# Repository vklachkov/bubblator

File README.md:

# Bubblator

> [!WARNING]
> This project is unfinished. Nothing is known to work yet. Do not use this board with real bubble-memory modules. It may damage rare hardware. Please wait for tested hardware, firmware, and clear operating instructions.

Bubblator is an experimental board for reading, writing, and attempting to restore Intel 7110 bubble-memory modules.

It follows the Intel Bubble Memory System design and uses the following main parts:

- Intel 7110 / 7110A(Z) One Megabit Bubble Memory Unit
- Intel 7220-1 Bubble Memory Controller
- Intel 7230 Current Pulse Generator
- Intel 7242 Formatter/Sense Amplifier
- Intel 7250 Coil Predriver
- 2x Intel 7254 driver transistors
- Arduino Nano

Firmware serial commands are described in [firmware/COMMANDS.md](firmware/COMMANDS.md).

## Documentation Used

The following Intel documents were used during development:

- [Megabits to Megabytes: Bubble Memory System Design and Board Layout (AP-187, 1984)](https://archive.org/details/bitsavers_intelbubbl87MegabitsToMegabytesBubbleMemorySystemD_3867950) - system design, board layout, and implementation guidance.
- [Intel Bubble Memory Design Handbook](https://archive.org/details/IntelBubbleMemoryDesignHandbook) - bubble-memory principles and design reference.
- [Intel BPK72 Bubble Storage Prototype Kit](https://web.archive.org/web/20190419090939/https://www.wolfgangrobel.de/museum/files_bubble5/intel%20BPK72%20Prototype%20kit%20users%20manual.pdf) - reference prototype system and kit documentation.
- [Intel 7220 Controller for 1Mbit BPK 70A Bubble Memory Subsystem](https://web.archive.org/web/20250912182130/https://wolfgangrobel.de/museum/files_bubble5/intel%207220%20bubble%20memory%20controller.pdf) - datasheet for the Intel 7220 bubble-memory controller.

Further project background:
- [ArduBubble / ReBubbling on the Unix Haters Wiki](https://wiki.unix-haters.org/doku.php?id=grid:rebubbling)

## Authors

- **sabur** - original firmware code.
- **grm** - initial hardware design.
- **BOOtak** - created the second PCB revision and assembled the prototype.
- **vklachkov** - continued the work of others.

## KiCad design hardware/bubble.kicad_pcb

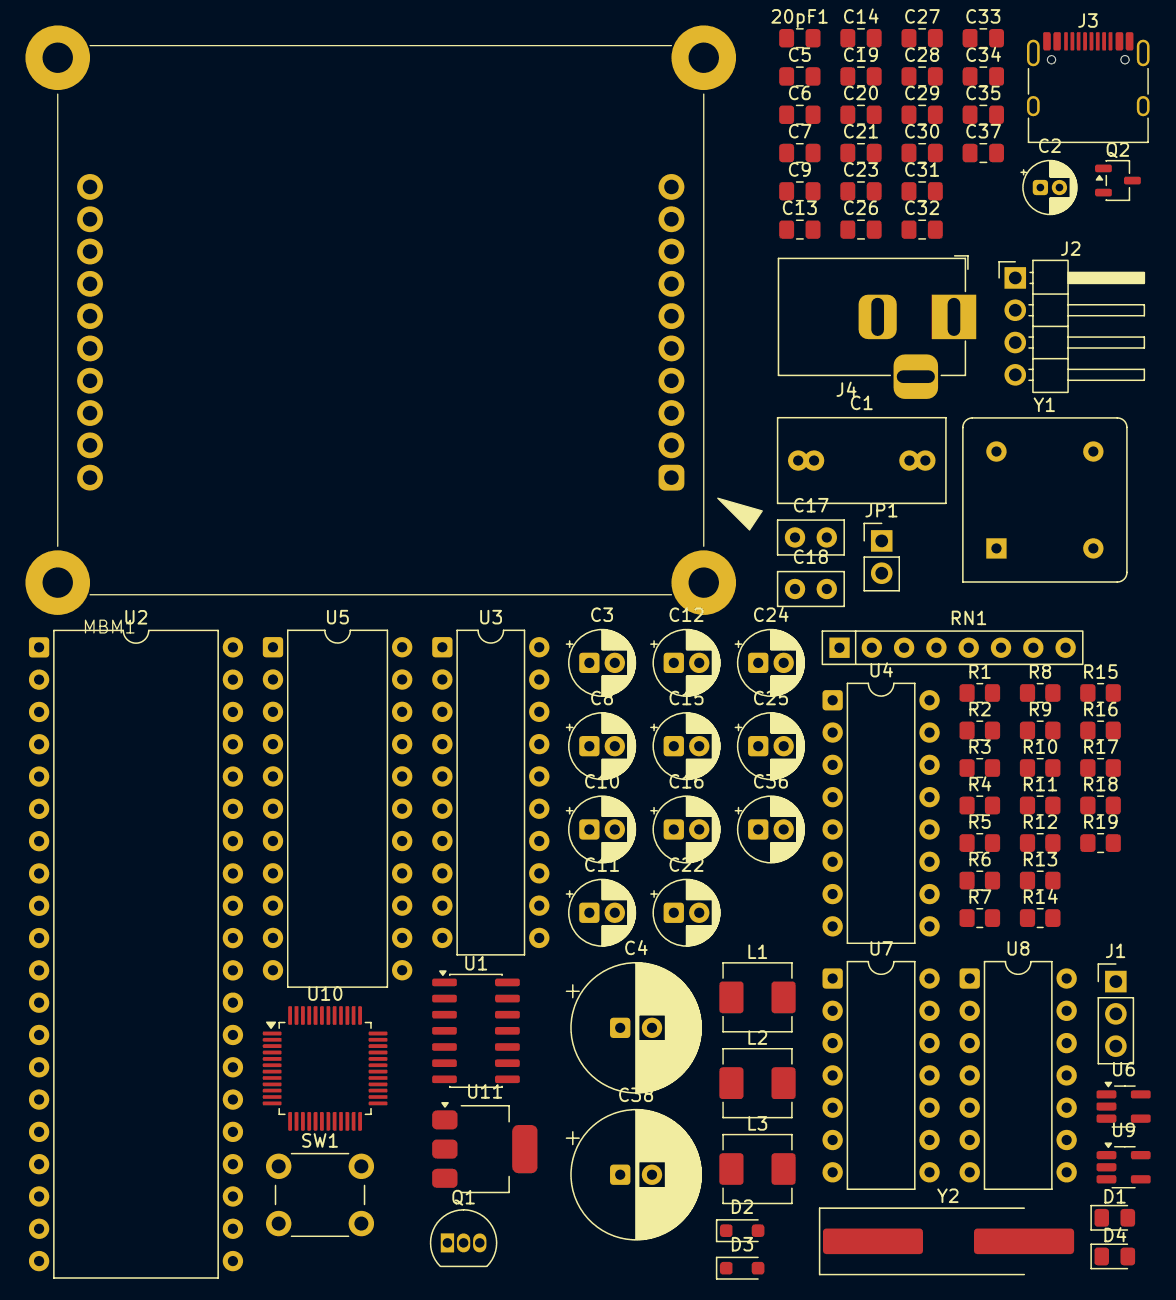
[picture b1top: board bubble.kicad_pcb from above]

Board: 4 copper layers, 88 parts (0 on the bottom side), 103 nets, no tracks yet.

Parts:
20pF1: C; C_0805_2012Metric_Pad1.18x1.45mm_HandSolder
C1: 0.33 uF; C_Rect_L13.0mm_W6.5mm_P7.50mm_P10.00mm
C2: 22uF; CP_Radial_D4.0mm_P1.50mm
C3, C8, C10, C11, C36: 47uF; CP_Radial_D5.0mm_P2.00mm
C4, C38: 150uF; CP_Radial_D10.0mm_P2.50mm
C5, C6, C7, C9, C13, C14, C19, C20, C21, C31, C32, C33, C35, C37: 0.1uF; C_0805_2012Metric_Pad1.18x1.45mm_HandSolder
C12, C15, C22, C24, C25: 22uF; CP_Radial_D5.0mm_P2.00mm
C16: 22uF 25V; CP_Radial_D5.0mm_P2.00mm
C17, C18: 120 pF 100V 5%; C_Disc_D5.0mm_W2.5mm_P2.50mm
C23: 2.2 uF; C_0805_2012Metric_Pad1.18x1.45mm_HandSolder
C26, C27: 0.01 uF; C_0805_2012Metric_Pad1.18x1.45mm_HandSolder
C28: 10 uF; C_0805_2012Metric_Pad1.18x1.45mm_HandSolder
C29: 20pF; C_0805_2012Metric_Pad1.18x1.45mm_HandSolder
C30, C34: 22uF; C_0805_2012Metric_Pad1.18x1.45mm_HandSolder
D1: POWER FAILED LED; LED_0805_2012Metric_Pad1.15x1.40mm_HandSolder
D2, D3: D; D_SOD-323_HandSoldering
D4: LED; LED_0805_2012Metric_Pad1.15x1.40mm_HandSolder
J1: Conn_01x03_Pin; PinHeader_1x03_P2.54mm_Vertical
J2: Conn_01x04_Pin; PinHeader_1x04_P2.54mm_Horizontal
J3: USB-C; USB_C_Receptacle_HRO_TYPE-C-31-M-12
J4: 12V Power; BarrelJack_Horizontal
JP1: Only for reseed; PinHeader_1x02_P2.54mm_Vertical
L1, L2, L3: 0.22 uH; L_APV_APH0530
MBM1: i7110; MBM_socket
Q1: BS170; TO-92_Inline
Q2: DTC113Z; SOT-23-3
R1, R2, R13, R15, R16: 5.1k; R_0805_2012Metric_Pad1.20x1.40mm_HandSolder
R3: 3.48k; R_0805_2012Metric_Pad1.20x1.40mm_HandSolder
R4: 10; R_0805_2012Metric_Pad1.20x1.40mm_HandSolder
R5: 300; R_0805_2012Metric_Pad1.20x1.40mm_HandSolder
R6: 47; R_0805_2012Metric_Pad1.20x1.40mm_HandSolder
R7: 1k; R_0805_2012Metric_Pad1.20x1.40mm_HandSolder
R8: 3.9k; R_0805_2012Metric_Pad1.20x1.40mm_HandSolder
R9: 5.5k; R_0805_2012Metric_Pad1.20x1.40mm_HandSolder
R10: 33k; R_0805_2012Metric_Pad1.20x1.40mm_HandSolder
R11, R12: 5.1; R_0805_2012Metric_Pad1.20x1.40mm_HandSolder
R14: 300Ohm; R_0805_2012Metric_Pad1.20x1.40mm_HandSolder
R17, R18: 22; R_0805_2012Metric_Pad1.20x1.40mm_HandSolder
R19: 1.5k; R_0805_2012Metric_Pad1.20x1.40mm_HandSolder
RN1: 1k; R_Array_SIP8
SW1: Reset; SW_PUSH_6mm_H5mm
U1: 74LS74; SOIC-14_3.9x8.7mm_P1.27mm
U2: i7220; DIP-40_W15.24mm
U3: i7242; DIP-20_W7.62mm
U4: i7250; DIP-16_W7.62mm
U5: i7230; DIP-22_W10.16mm
U6: 74AHC1G00; SOT-23-5_HandSoldering
U7, U8: i7254; DIP-14_W7.62mm
U9: 74LVC1G07; SOT-23-5_HandSoldering
U10: STM32F103C8Tx; LQFP-48_7x7mm_P0.5mm
U11: AMS1117-3.3; SOT-223-3_TabPin2
Y1: 8.000 MHz; Oscillator_DIP-8
Y2: 8Mhz; Crystal_SMD_HC49-SD_HandSoldering

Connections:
+3.3V: C33.1, C34.1, J1.3, J2.4, R19.2, U10.9 (VDDA), U10.24 (VDD), U10.36 (VDD), U10.48 (VDD), U11.2 (VO)
+5V: C5.1, C8.1, C11.1, C13.1, C30.1, C32.1, C35.2, C36.2, D1.2 (A), J3.A4 (VBUS), J3.A9 (VBUS), J3.B4 (VBUS), J3.B9 (VBUS), L1.2, R1.1, R2.1, R7.1, R13.2, U1.1 (~R), U1.4 (~S), U1.14 (VCC), U2.40 (VCC), U3.20 (VCC), U6.5 (VCC), U9.5 (VCC), U11.3 (VI), Y1.1 (EN), Y1.8 (Vcc)
+12V: C9.1, C10.1, C12.1, C20.1, C21.1, C24.1, C25.1, C37.1, C38.1, J4.1, JP1.2 (B), L2.2, R4.2, R6.2, R11.2, U4.16 (VDD), U7.6 (S2), U7.13 (S4), U8.6 (S2), U8.13 (S4)
/MBM/7230 VCC: C4.1, C7.1, L3.1, U5.22 (VCC)
/MBM/7230 VDD: C2.1, C3.1, C6.1, L2.1, U5.1 (VDD)
/MBM/~7220 POWER.FAIL: C23.1, C26.1, D3.2 (A), Q2.3 (C), R8.2, U2.1 (~PWR.FAIL)
/MBM/~7220 RESET.OUT: R13.1, U2.2 (~RESET.OUT), U6.2, U9.2
A0: U2.10 (A0), U10.42 (PB6)
BOOT: J1.2, U10.44 (BOOT0)
CLK: U1.5 (Q), U2.3 (CLK), U3.18 (CLK), U10.3 (PC14)
D0: U2.11 (D0), U10.43 (PB7)
D1: U2.12 (D1), U10.45 (PB8)
D2: U2.13 (D2), U10.46 (PB9)
D3: U2.14 (D3), U10.21 (PB10)
D4: U2.15 (D4), U10.22 (PB11)
D5: U2.16 (D5), U10.25 (PB12)
D6: U2.17 (D6), U10.26 (PB13)
D7: U2.18 (D7), U10.27 (PB14)
D8: U2.19 (D8), U10.28 (PB15)
DRQ: U2.8 (DRQ), U10.29 (PA8)
GND: 20pF1.1, C1.2, C2.2, C3.2, C4.2, C5.2, C6.2, C7.2, C8.2, C9.2, C10.2, C11.2, C12.2, C13.2, C14.2, C15.2, C20.2, C21.2, C23.2, C24.2, C25.2, C26.2, C27.2, C28.2, C29.1, C30.2, C31.1, C32.2, C33.2, C34.2, C35.1, C36.1, C37.2, C38.2, J1.1, J2.1, J3.A1 (GND), J3.A12 (GND), J3.B1 (GND), J3.B12 (GND), J3.SH (SHIELD), J4.2, Q1.3 (S), Q2.2 (E), R10.2, R12.1, R14.1, R15.2, R16.1, SW1.2, U1.7 (GND), U2.20 (GND), U3.1 (~CS), U3.10 (GND), U4.8 (GND), U5.11 (GND), U5.12 (GND), U6.3 (GND), U7.2 (S1), U7.9 (S3), U8.2 (S1), U8.9 (S3), U9.3 (GND), U10.8 (VSSA), U10.23 (VSS), U10.35 (VSS), U10.47 (VSS), U11.1 (GND), Y1.4 (GND)
INT: U2.9 (INT), U10.39 (PB3)
NRST: C31.2, SW1.1, U10.7 (NRST)
unnamed: C1.1, L1.1, L3.2
unnamed: C16.2, MBM1.1 (PULSE.COM(+12V)), MBM1.6 (PULSE.COM(+12V))
unnamed: D1.1 (K), R5.2
unnamed: D2.1 (K), R8.1
unnamed: D3.1 (K), R9.1
unnamed: D4.1 (K), R14.2
unnamed: J3.A5 (CC1), R15.1
unnamed: J3.B5 (CC2), R16.2
unnamed: J3.A6 (D+), J3.B6 (D+), R18.1, R19.1
unnamed: J3.A7 (D-), J3.B7 (D-), R17.1
unnamed: C16.1, JP1.1 (A), R6.1
unnamed: MBM1.4 (BOOT.REP), U5.13 (BOOT.REP)
unnamed: MBM1.5 (BOOT.SWAP), U5.14 (BOOT.SWAP)
unnamed: C19.2, C22.2, MBM1.15 (DET.COM), R12.2
unnamed: MBM1.19 (DET.OUT.A+), RN1.5 (R4.2)
unnamed: MBM1.18 (DET.OUT.A-), RN1.6 (R3.2)
unnamed: MBM1.17 (DET.OUT.B+), RN1.7 (R2.2)
unnamed: MBM1.16 (DET.OUT.B-), RN1.8 (R1.2)
unnamed: C19.1, C22.1, MBM1.20 (DET.SUPPLY), R11.1
unnamed: MBM1.7 (GEN.A), U5.18 (GEN.A)
unnamed: MBM1.8 (GEN.B), U5.19 (GEN.B)
unnamed: MBM1.3 (REP.A), U5.15 (REP.A)
unnamed: MBM1.2 (REP.B), U5.16 (REP.B)
unnamed: MBM1.13 (SWAP.A), MBM1.14 (SWAP.B), U5.17 (SWAP)
unnamed: MBM1.10 (X+.COIL.IN), U7.7 (D2), U7.8 (D3)
unnamed: MBM1.9 (X-.COIL.IN), U7.1 (D1), U7.14 (D4)
unnamed: MBM1.12 (Y+.COIL.IN), U8.1 (D1), U8.14 (D4)
unnamed: MBM1.11 (Y-.COIL.IN), U8.7 (D2), U8.8 (D3)
unnamed: Q1.1 (D), R3.1
unnamed: Q2.1 (B), U6.4
unnamed: C18.2, RN1.1 (R1.1), U3.9 (DET.B-)
unnamed: C18.1, RN1.2 (R2.1), U3.8 (DET.B+)
unnamed: C17.2, RN1.3 (R3.1), U3.7 (DET.A-)
unnamed: C17.1, RN1.4 (R4.1), U3.6 (DET.A+)
unnamed: U1.3 (C), Y1.5 (OUT)
unnamed: U1.2 (D), U1.6 (~Q)
unnamed: U2.29 (C/~D), U3.3 (C/~D)
unnamed: U2.22 (DIO), U3.17 (DIO)
unnamed: U2.32 (~BOOT.EN), U5.10 (~BOOT.EN)
unnamed: U2.30 (~BOOT.SW.EN), U5.9 (~BOOT.SW.EN)
unnamed: U2.33 (~REP.EN), U5.8 (~REP.EN)
unnamed: U2.24 (~SHIFT.CLK), U3.15 (~SHIFT.CLK)
unnamed: U2.31 (~SWAP.EN), U5.6 (~SWAP.EN)
unnamed: U2.23 (~SYNC), U3.19 (~SELECT.IN)
unnamed: U2.35 (~TM.A), U5.2 (~TM.A)
unnamed: U2.34 (~TM.B), U5.3 (~TM.B)
unnamed: U2.39 (~X+), U4.3 (~X+.IN)
unnamed: U2.38 (~X-), U4.4 (~X-.IN)
unnamed: U2.37 (~Y+), U4.5 (~Y+.IN)
unnamed: U2.36 (~Y-), U4.6 (~Y-.IN)
unnamed: C14.1, C15.1, R4.1, U3.5 (VDD)
unnamed: U3.11 (~DATA.OUT.A), U5.5 (~GEN.EN.A)
unnamed: U3.12 (~DATA.OUT.B), U5.4 (~GEN.EN.B)
unnamed: U3.13 (~ENABLE.A), U4.1 (~CS), U5.7 (~CS)
unnamed: U4.14 (X+.OUT), U7.3 (G1)
unnamed: U4.12 (X-.OUT), U7.10 (G3)
unnamed: U4.10 (Y+.OUT), U8.10 (G3)
unnamed: U4.7 (Y-.OUT), U8.3 (G1)
unnamed: U4.15 (~X+.OUT), U7.5 (G2)
unnamed: U4.13 (~X-.OUT), U7.12 (G4)
unnamed: U4.11 (~Y+.OUT), U8.12 (G4)
unnamed: U4.9 (~Y-.OUT), U8.5 (G2)
unnamed: R3.2, U5.20 (REFR)
unnamed: C29.2, U10.5 (PD0), Y2.2
unnamed: 20pF1.2, U10.6 (PD1), Y2.1
STATUS_LED: D4.2 (A), U10.2 (PC13)
SWCLK: J2.2, U10.37 (PA14)
SWDIO: J2.3, U10.34 (PA13)
USB_D+: R18.2, U10.33 (PA12)
USB_D-: R17.2, U10.32 (PA11)
~BUS.RD: U2.25 (~BUS.RD), U10.31 (PA10)
~CS: U2.21 (~CS), U10.4 (PC15)
~DACK: U2.7 (~DACK), U10.30 (PA9)
~DET.ON: U2.28 (~DET.ON), U10.40 (PB4)
~ERR_FLAG: R1.2, U2.27 (~ERR.FLG), U3.4 (~ERR.FLG), U10.41 (PB5)
~POWER.FAIL: C27.1, D2.2 (A), R5.1, R7.2, U2.4 (~RESET), U5.21 (~PWR.FAIL), U6.1
~RD: U2.5 (~RD), U10.18 (PB0)
~RESET.BUS: C28.1, Q1.2 (G), R9.2, R10.1, U3.16 (~RESET), U4.2 (~RESET), U9.4, U10.38 (PA15)
~WAIT: R2.2, U2.26 (~WAIT), U10.20 (PB2)
~WR: U2.6 (~WR), U10.19 (PB1)
